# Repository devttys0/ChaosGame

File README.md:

# The Chaos Game Circuit

An analog circuit that calculates and plots fractals on an XY plot using chaos theory.

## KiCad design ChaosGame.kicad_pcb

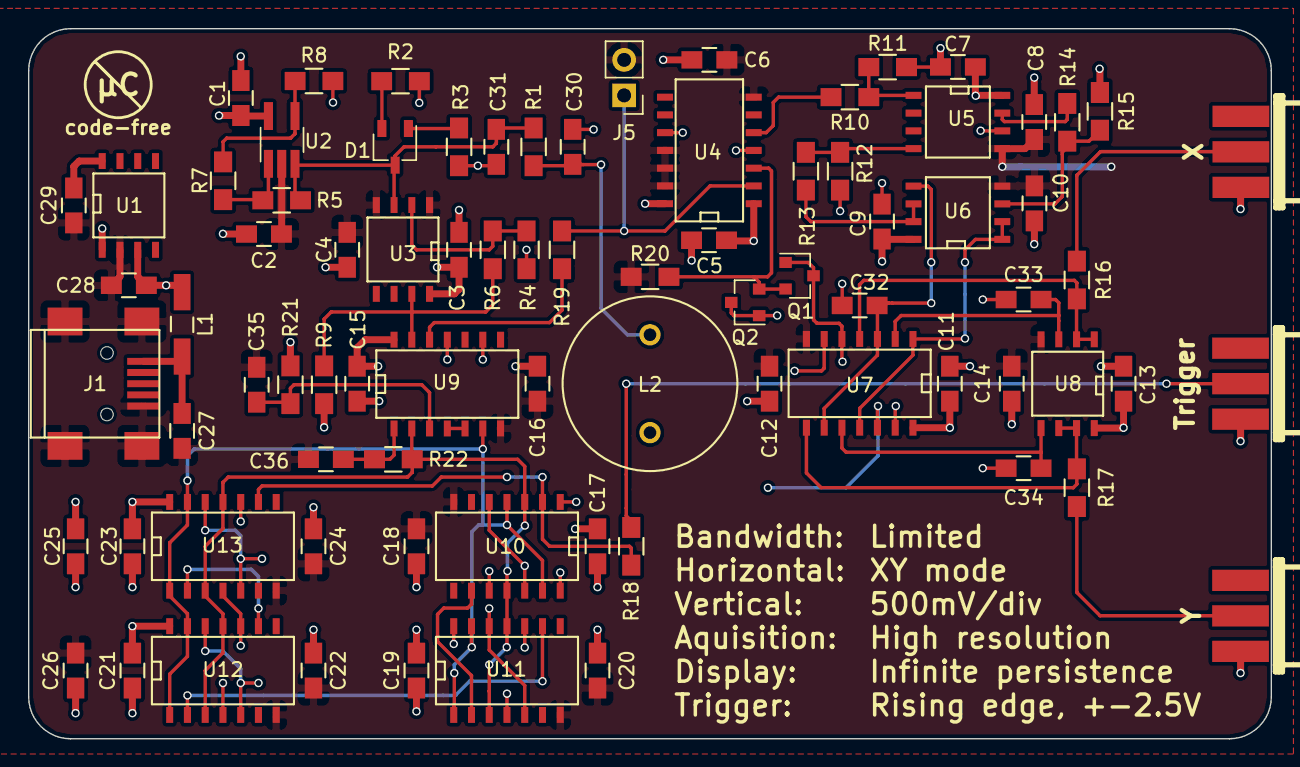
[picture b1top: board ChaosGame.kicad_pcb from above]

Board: 4 copper layers, 88.9 x 50.8 mm, 81 parts (0 on the bottom side), 44 nets.

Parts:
C1, C2, C3, C4, C5, C6, C7, C8, C9, C10, C11, C12, C13, C14, C15, C16, C17, C18, C19, C20, C21, C22, C23, C24, C27, C29, C30, C35, C36: 0.1uF; C_0805_HandSoldering
C25, C26, C28: 10uF; C_0805_HandSoldering
C31: 0.01uF; C_0805_HandSoldering
C32, C33, C34: 1500pF; C_0805_HandSoldering
D1: BAT54S; TSOT-23
J1: USB_OTG; USB_Mini-B
J5: RNG; Pin_Header_Straight_1x02_Pitch2.54mm
L1: FB; Choke_SMD_1206_Handsoldering
L2: 15mH; RLB1314-153
Q1, Q2: 2N3904; SOT-23
R1: 1.37k; R_0805_HandSoldering
R2, R3, R16, R17, R18, R19, R20: 2.2k; R_0805_HandSoldering
R4: 100k; R_0805_HandSoldering
R5, R7, R8, R9: 1k; R_0805_HandSoldering
R6: 1M; R_0805_HandSoldering
R10, R13: 15k; R_0805_HandSoldering
R11, R12, R15: 10k; R_0805_HandSoldering
R14: 0; R_0805_HandSoldering
R21: 10M; R_0805_HandSoldering
R22: 56k; R_0805_HandSoldering
Trigger: Trigger; CON-SMA-EDGE
U1: TLE2426; SOIC-8-N
U2: TLV271; TSOT-23-5_HandSoldering
U3: LM311; SOIC-8-N
U4, U10, U11, U12, U13: 74HC74; SOIC-14_N
U5: INA826; SOIC-8-N
U6, U8: TLV272; SOIC-8-N
U7: 4066; SOIC-14_N
U9: 74HC14; SOIC-14_N
X: X; CON-SMA-EDGE
Y: Y; CON-SMA-EDGE

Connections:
+VDC: C1.1, C3.1, C5.1, C7.1, C9.1, C11.1, C13.1, C15.1, C17.1, C19.1, C21.1, C23.1, C25.1, C28.1, L1.2, R9.1, R21.1, U1.3, U2.5, U3.8, U4.1, U4.4, U4.10, U4.14, U5.8, U6.8, U7.14, U8.8, U9.9, U9.11, U9.14, U10.1, U10.10, U10.14, U11.4, U11.10, U11.14, U12.4, U12.10, U12.14, U13.4, U13.10, U13.14
-VDC: C2.2, C4.2, C6.2, C8.2, C10.2, C12.2, C14.2, C16.2, C18.2, C20.2, C22.2, C24.2, C26.2, C27.2, C28.2, C29.2, C35.2, C36.2, J1.5, J1.6, J5.2, R20.2, U1.2, U2.2, U3.1, U3.4, U4.7, U4.11, U4.12, U4.13, U5.5, U6.4, U7.7, U8.4, U9.7, U10.7, U11.7, U12.7, U13.7
CHUA_ATTRACTOR: R19.1, U9.12
CLOCK: R22.2, U9.2, U10.3, U10.11, U11.3, U11.11, U12.3, U12.11, U13.3, U13.11
CLOCK_CYCLE_0: Q1.1, Q1.3, U7.5, U10.5, U10.12
CLOCK_CYCLE_1: U7.13, U11.5, U11.12
CLOCK_CYCLE_2: Q2.1, Q2.3, U7.6, U12.5, U12.12
CLOCK_CYCLE_3: U7.12, U13.5, U13.12
COORDINATE: R10.1, U4.5
FRACTAL_TRIGGER: R18.1, U10.2, U13.9
FRACTAL_X: R16.1, U7.4, U8.1, U8.2
FRACTAL_Y: R17.1, U7.8, U8.6, U8.7
GNDREF: C1.2, C2.1, C3.2, C4.1, C5.2, C6.1, C7.2, C8.1, C9.2, C10.1, C11.2, C12.1, C13.2, C14.1, C15.2, C16.1, C17.2, C18.1, C19.2, C20.1, C21.2, C22.1, C23.2, C24.1, C25.2, C26.1, C30.2, C31.2, C32.2, C33.2, C34.2, L2.1, R2.2, R3.2, R4.2, R8.2, R11.2, R12.2, R15.2, Trigger.2, U1.1, U5.6, X.2, Y.2
unnamed: C27.1, J1.1, L1.1
unnamed: C29.1, U1.8
unnamed: C30.1, L2.2, R1.1
unnamed: C31.1, D1.3, R1.2, R5.1, U2.3, U3.3
unnamed: C32.1, U6.5, U7.3, U7.9
unnamed: C33.1, U7.2, U8.3
unnamed: C34.1, U7.10, U8.5
unnamed: C35.1, R21.2, U9.3
unnamed: C36.1, R22.1, U9.1
unnamed: D1.1, R3.1
unnamed: D1.2, R2.1
unnamed: R16.2, X.1
unnamed: R17.2, Y.1
unnamed: R18.2, Trigger.1
unnamed: J5.1, R19.2, U4.2
unnamed: Q1.2, Q2.2, R20.1, U4.3
unnamed: R4.1, R6.2, U3.2
unnamed: R5.2, R7.1, U2.1
unnamed: R6.1, R9.2, U3.7, U9.13
unnamed: R7.2, R8.1, U2.4
unnamed: R10.2, R11.1, U5.1
unnamed: R12.1, R13.1, U5.4
unnamed: R13.2, U6.6, U6.7
unnamed: R14.1, U5.7
unnamed: R14.2, R15.1, U6.3
unnamed: U6.1, U6.2, U7.1, U7.11
unnamed: U9.4, U9.5
unnamed: U10.9, U11.2
unnamed: U11.9, U12.2
unnamed: U12.9, U13.2
RESET: U9.6, U10.4, U10.13, U11.1, U11.13, U12.1, U12.13, U13.1, U13.13

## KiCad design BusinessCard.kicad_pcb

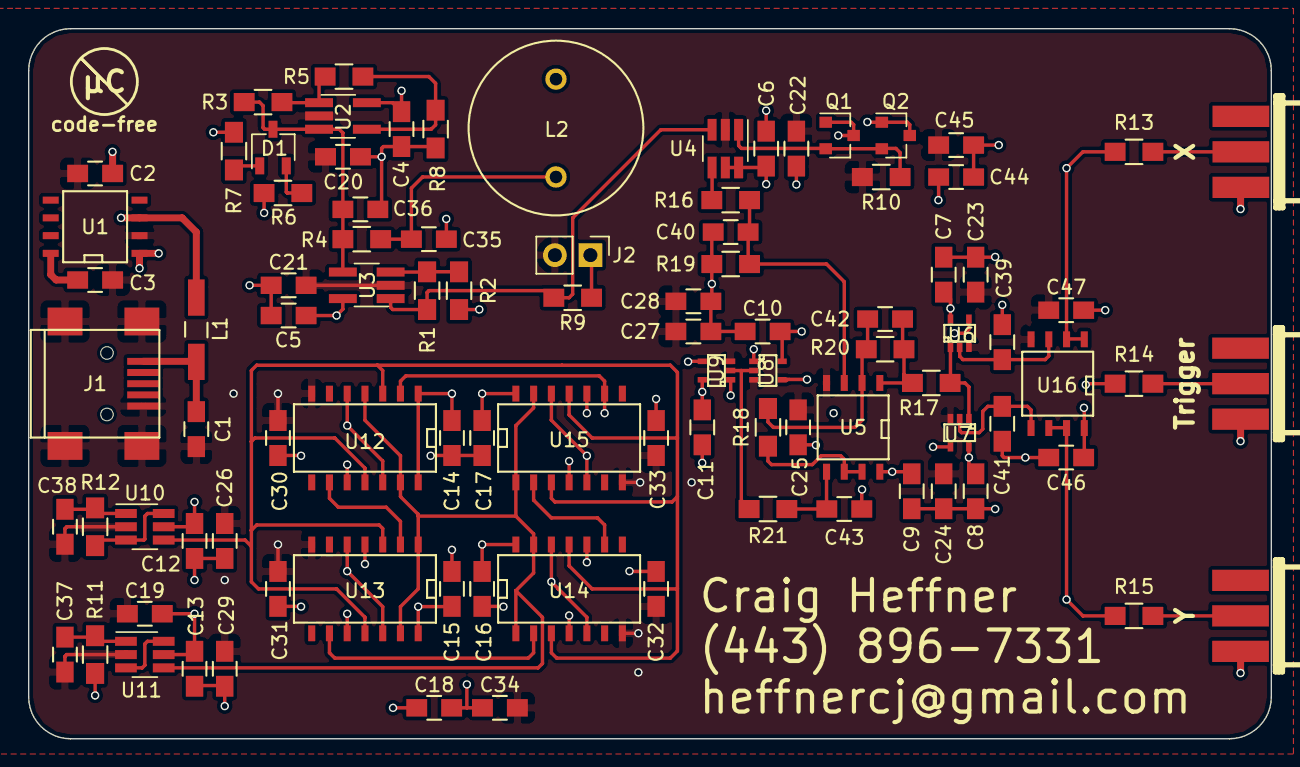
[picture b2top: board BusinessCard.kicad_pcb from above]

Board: 4 copper layers, 88.9 x 50.8 mm, 94 parts (0 on the bottom side), 44 nets.

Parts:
C1, C3, C4, C5, C6, C7, C8, C9, C10, C11, C12, C13, C14, C15, C16, C17, C20, C21, C22, C23, C24, C25, C26, C27, C28, C29, C30, C31, C32, C33, C35, C37, C38, C46, C47: 0.1uF; C_0805_HandSoldering
C2, C18, C19, C34, C44, C45: 10uF; C_0805_HandSoldering
C36: 0.01uF; C_0805_HandSoldering
C39, C40, C41, C42, C43: 1500pF; C_0805_HandSoldering
D1: BAT54S; TSOT-23
J1: USB_OTG; USB_Mini-B
J2: RNG; Pin_Header_Straight_1x02_Pitch2.54mm
J3: X; CON-SMA-EDGE
J4: Trigger; CON-SMA-EDGE
J5: Y; CON-SMA-EDGE
L1: FB; Choke_SMD_1206_Handsoldering
L2: 15mH; RLB1314-153
Q1, Q2: MMBT3904; SOT-23
R1: 1M; R_0805_HandSoldering
R2: 100k; R_0805_HandSoldering
R3, R5, R8, R19, R20: 1k; R_0805_HandSoldering
R4: 1.37k; R_0805_HandSoldering
R6, R7, R9, R10, R13, R14, R15: 2.2k; R_0805_HandSoldering
R11: 10M; R_0805_HandSoldering
R12: 56k; R_0805_HandSoldering
R16, R18: 1.5k; R_0805_HandSoldering
R17, R21: 100; R_0805_HandSoldering
U1: TLE2426; SOIC-8-N
U2: TLV271; TSOT-23-5_HandSoldering
U3: TLV3201; TSOT-23-5_HandSoldering
U4: SN74LVC1G175; SOT-23-6_Handsoldering
U5, U16: TLV272; SOIC-8-N
U6, U7, U8, U9: SN74LVC1G66; SC-70-5
U10, U11: SN74LVC2G14DBVR; SOT-23-6_Handsoldering
U12, U13, U14, U15: 74HC74; SOIC-14_N

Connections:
+VDC: C2.1, C4.1, C5.1, C6.1, C7.1, C8.1, C9.1, C10.1, C11.1, C12.1, C13.1, C14.1, C15.1, C16.1, C17.1, C18.1, C19.1, C44.1, C46.1, L1.2, R11.1, U1.3, U2.5, U3.5, U4.5, U4.6, U5.8, U6.5, U7.5, U8.5, U9.5, U10.5, U11.5, U12.1, U12.10, U12.14, U13.4, U13.10, U13.14, U14.4, U14.10, U14.14, U15.4, U15.10, U15.14, U16.8
-VDC: C1.2, C2.2, C3.2, C19.2, C20.2, C21.2, C22.2, C23.2, C24.2, C25.2, C26.2, C27.2, C28.2, C29.2, C30.2, C31.2, C32.2, C33.2, C34.2, C37.2, C38.2, C45.2, C47.2, J1.5, J1.6, J2.2, R10.2, U1.2, U2.2, U3.2, U4.2, U5.4, U6.3, U7.3, U8.3, U9.3, U10.2, U11.2, U12.7, U13.7, U14.7, U15.7, U16.4
CHUA_ATTRACTOR: R1.1, R9.1, U3.1, U4.3
CLOCK: U10.4, U12.3, U12.11, U13.3, U13.11, U14.3, U14.11, U15.3, U15.11
CLOCK_CYCLE_0: Q1.1, Q1.3, U8.4, U12.5, U12.12
CLOCK_CYCLE_1: U6.4, U13.5, U13.12
CLOCK_CYCLE_2: Q2.1, Q2.3, U9.4, U14.5, U14.12
CLOCK_CYCLE_3: U7.4, U15.5, U15.12
COORDINATE: R16.1, U4.4
FRACTAL_TRIGGER: R14.1, U12.2, U15.9
FRACTAL_X: R13.1, U8.1, U16.1, U16.2
FRACTAL_Y: R15.1, U9.1, U16.6, U16.7
GNDREF: C4.2, C5.2, C6.2, C7.2, C8.2, C9.2, C10.2, C11.2, C12.2, C13.2, C14.2, C15.2, C16.2, C17.2, C18.2, C20.1, C21.1, C22.1, C23.1, C24.1, C25.1, C26.1, C27.1, C28.1, C29.1, C30.1, C31.1, C32.1, C33.1, C34.1, C35.2, C36.2, C39.2, C40.2, C41.2, C43.2, C44.2, C45.1, C46.2, C47.1, J3.2, J4.2, J5.2, L2.1, R2.2, R6.2, R7.2, R8.2, R19.2, U1.1
unnamed: C1.1, J1.1, L1.1
unnamed: C3.1, U1.8
unnamed: C35.1, L2.2, R4.1
unnamed: C36.1, D1.3, R3.1, R4.2, U2.3, U3.4
unnamed: C37.1, R11.2, U11.1
unnamed: C38.1, R12.1, U10.1
unnamed: C39.1, U6.2, U16.3
unnamed: C40.1, R16.2, R19.1, U5.3
unnamed: C41.1, U7.2, U16.5
unnamed: C42.1, R17.2, R20.1, U5.1
unnamed: C42.2, R18.2, R20.2, U5.2
unnamed: C43.1, R21.2, U5.5
unnamed: D1.1, R7.1
unnamed: D1.2, R6.1
unnamed: J2.1, R9.2
unnamed: J3.1, R13.2
unnamed: J4.1, R14.2
unnamed: J5.1, R15.2
unnamed: Q1.2, Q2.2, R10.1, U4.1
unnamed: R1.2, R2.1, U3.3
unnamed: R3.2, R5.1, U2.1
unnamed: R5.2, R8.1, U2.4
unnamed: R12.2, U10.3, U10.6
unnamed: R17.1, U6.1, U7.1
unnamed: R18.1, U5.6, U5.7
unnamed: R21.1, U8.2, U9.2
unnamed: U11.3, U11.6
unnamed: U12.9, U13.2
unnamed: U13.9, U14.2
unnamed: U14.9, U15.2
RESET: U11.4, U12.4, U12.13, U13.1, U13.13, U14.1, U14.13, U15.1, U15.13

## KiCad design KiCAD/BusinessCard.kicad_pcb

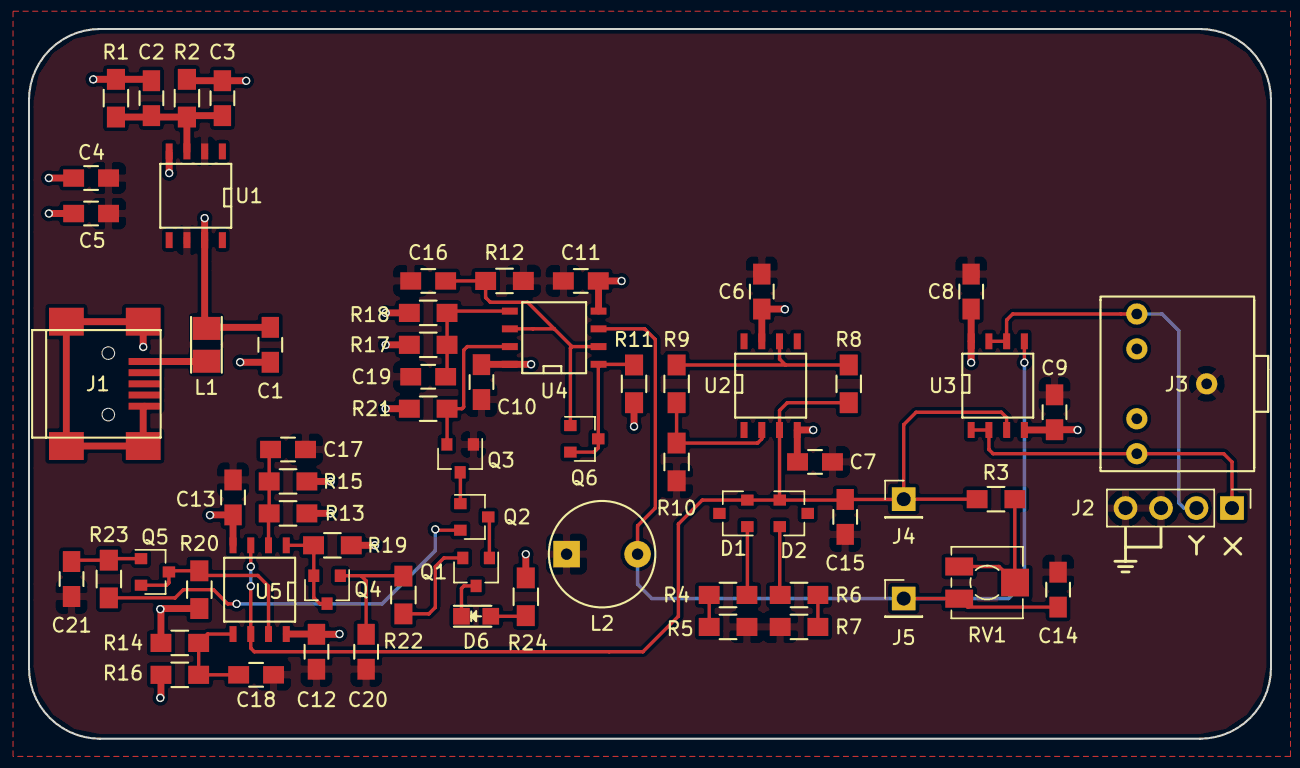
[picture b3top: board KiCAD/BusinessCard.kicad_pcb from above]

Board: 4 copper layers, 88.9 x 50.8 mm, 67 parts (0 on the bottom side), 32 nets.

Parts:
C1, C4, C5: 10uF; C_0805_HandSoldering
C2, C3, C14, C16, C17, C18, C19, C20, C21: 0.1uF; C_0805_HandSoldering
C6, C7, C8, C9, C10, C11, C12, C13, C15: 0.01uF; C_0805_HandSoldering
D1, D2: BAT54; SOT-23
D6: LED; LED_0805
J1: USB_OTG; USB_Mini-B
J2: XY Out; Pin_Header_Straight_1x04_Pitch2.54mm
J3: XY OUT; SJ1-352XN
J4: X; Pin_Header_Straight_1x01_Pitch2.54mm
J5: Y; Pin_Header_Straight_1x01_Pitch2.54mm
L1: 100nH; Inductor_Taiyo-Yuden_NR-20xx_HandSoldering
L2: 18mH; INDUCTOR_V
Q1, Q2, Q3, Q4, Q5, Q6: 2N3904; SOT-23
R1, R2, R3, R4, R5, R6, R7, R8, R9, R10: 1k; R_0805_HandSoldering
R11, R12, R14, R15, R18, R22, R23: 10k; R_0805_HandSoldering
R13, R16, R19, R20, R21: 6.8k; R_0805_HandSoldering
R17: 8.2k; R_0805_HandSoldering
R24: 100; R_0805_HandSoldering
RV1: 1k; Potentiometer_Trimmer_Vishay_TS53YJ
U1, U2: MCP601; SOIC-8-N
U3: MCP602; SOIC-8-N
U4, U5: LM393; SOIC-8-N

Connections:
+VDC: C1.1, C2.1, C4.1, C6.1, C8.1, C10.1, C12.1, L1.2, R1.1, R11.1, R13.2, R14.2, R17.2, R19.1, R20.1, R21.1, R24.1, U1.7, U2.7, U3.8, U4.8, U5.8
-VDC: C1.2, C3.2, C5.2, C7.2, C9.2, C11.2, C13.2, J1.5, J1.6, R2.2, R15.2, R16.2, R18.2, U1.4, U2.4, U3.4, U4.4, U5.4
GND: C4.2, C5.1, C6.2, C7.1, C8.2, C9.1, C10.2, C11.1, C12.2, C13.1, C14.2, C15.2, C16.2, C17.2, C18.2, C19.2, C20.2, C21.2, J2.3, J2.4, J3.3, L2.1, Q3.1, R5.2, R7.2, R10.2, R12.2, U1.2, U1.6
unnamed: C2.2, C3.1, R1.2, R2.1, U1.3
unnamed: C16.1, Q6.1, R12.1, U4.2, U4.6
unnamed: C17.1, R13.1, R15.1, U5.2
unnamed: C18.1, R14.1, R16.1, U5.5
unnamed: C19.1, R17.1, R18.1, U4.5
unnamed: C20.1, Q4.1, R22.1
unnamed: C21.1, Q5.1, R23.1
unnamed: D1.1, R4.1
unnamed: D2.2, R6.1
unnamed: D6.1, Q1.3
unnamed: D6.2, R24.2
unnamed: J1.1, L1.1
unnamed: Q1.1, Q2.3
unnamed: Q1.2, R22.2
unnamed: Q2.1, Q3.3
unnamed: Q2.2, R23.2
unnamed: Q3.2, R21.2, U4.7
unnamed: Q4.2, Q4.3, R19.2, U5.1
unnamed: Q5.2, Q5.3, R20.2, U5.7
unnamed: Q6.2, Q6.3, R11.2, U4.1
unnamed: R3.1, RV1.2, RV1.3
unnamed: R4.2, R5.1
unnamed: R6.2, R7.1
unnamed: R8.2, R9.1, U2.6
unnamed: R9.2, R10.1, U2.2
X: C15.1, D1.2, D2.1, J4.1, R3.2, R8.1, U2.3, U3.3, U5.3, U5.6
X_OUT: J2.1, J3.2, U3.1, U3.2
Y: C14.1, J5.1, L2.2, RV1.1, U3.5, U4.3
Y_OUT: J2.2, J3.1, U3.6, U3.7

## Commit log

2018-01-08 Initial commit of KiCAD files
2018-01-09 Fixed digitizer comparator bugs. Updated documentation.
2018-02-03 New design checkin
2018-02-03 Added PCB file
2018-02-04 Updated to final schematic, netlist, and BOM for initial prototype PCB design
2018-02-05 Replaced GND with GNDREF; removed unecessary project specific footprint; new PCB outline ready for parts placement and routing.
2018-02-05 Power, output buffer, and analog switch placed.
2018-02-05 Fractal calculator placed.
2018-02-05 fractal coordinate selector placed.
2018-02-05 Started fractal clock placement
2018-02-06 All parts placed, routing incomplete.
2018-02-06 PCB routing finished.
2018-02-06 Removed silkscreen from on top of copper pads on SMA connector footprints.
2018-02-06 Generated gerbers with protel naming convention.
2018-02-10 Updated with different components for easier layout.
2018-02-10 Removed unused ina826.lib
2018-02-11 Generated new netlist
2018-02-12 All but the ring counter placed and routed.
2018-02-12 All parts placed, only routing of clock signals remain.
2018-02-12 Final PCB routing, generated Gerber files.
2018-02-13 Switched to SOIC packages for the op amps.
2018-02-14 Placing and routing complete.
2018-02-14 Generated gerber files
2018-03-04 Fixed pin numbering on Q1, Q2. Changed op amp part numbers.
2018-03-04 Replaced EOL diode D1.
2018-08-10 Renamed files to ChaosGame; implemented some changes from master.
2018-08-14 Final updates to PCB and schematics.
